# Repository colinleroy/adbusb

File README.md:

#  ADB to USB converter for Apple keyboards

Allow one ADB keyboard to be used on one ADB computer (old Macintosh and Apple IIgs) and one USB computer at the same time by switching between them.

## What works

- adb passthrough between a macintosh and keyboard/mouse + softpower
- adb keyboard to usb-hid conversion:
  - iso and ansi layouts
  - locking caps lock
  - power key in usb (translated as 0x66 "keyboard power")
- tested on multiple keyboards: aek ii, m0116/m0118, appledesign...
- tested on macintosh se
  
## What don't work yet

- keyboard leds on usb: the *keyboard* library doesn't handle hid output reports
- hotplugging adb: works randomly, the microcontroller don't seems to like that
- mouse passthrough in usb-hid mode
- correct keyboard detection by the macintosh when the board is in usb mode: not a problem in practice
- collision detection handling: the program calls the keyboard at address 2

## Hardware needed

- arduino pro micro because it works on 5V and is hid capable
- a resistor (1K - 10K ohm) for the pull up
- 2 mini-din 4 pin connectors
- 2-pin switch

## How to build it

- connect the switch between A3 (PF4) and GND
- connect GND on the two mini-din pins 4
- connect 9 (PB5) to the mini-din A pin 1 (computer adb line)
- connect 8 (PB4) to the mini-din A pin 2 (computer softpower line)
- connect VCC to the mini-din B pin 3 (keyboard power)
- connect 10 (PB6) to VCC through the resistor
- connect 10 (PB6) to the mini-din B pin 1 (keyboard adb line)
- connect 16 (PB2) to the mini-din B pin 2 (keyboard softpower line)
- mark the mini-din B as the keyboard connector

> [!CAUTION]
> i don't know what happens if you invert the connectors and inject external 5V into the macintosh adb

Mini-DIN female connector front view :
```
/------\
| 4  3 |
| 2  1 |
\__==__/
```

Arduino Pro Micro pinout :
```
                                ___________
                     PD3  TXD  |    USB    |  RAW
                     PD2   20  |           |  GND        --- keyboard pin 4
                          GND  |           |  RST
computer pin 4 ---        GND  |           |  VCC        --- keyboard pin 3 ---
                     PD1    2  |           |  A3   PF4                         |
                     PD0    3  |           |  A2   PF5                         _
                     PD4    4  |           |  A1   PF6                        | |
                     PC6    5  |           |  A0   PF7               resistor | |
                     PD7    6  |           |  15   PB1                        |_|
                     PE6    7  |           |  14   PB3                         |
computer pin 2 ---   PB4    8  |           |  16   PB2   --- keyboard pin 2    |
computer pin 1 ---   PB5    9  |___________|  10   PB6   --- keyboard pin 1 ---

```

## How to compile and upload it

1. install `arduino-cli`
2. `arduino-cli core install arduino:avr`
3. `arduino-cli lib install Keyboard`
4. compile this project by `cd` in then `arduino-cli compile --fqbn arduino:avr:micro`
5. connect the board to the computer
6. get board port with `arduino-cli board list`
7. upload it `arduino-cli upload -p /dev/.......`

## References

- [Guide to the Macintosh family hardware, Chapter 8 : Apple Desktop Bus, Apple, 1990](https://archive.org/details/apple-guide-macintosh-family-hardware/page/n325/mode/2up)
- [Apple Desktop Bus Protocol, lopaciuk.eu, 2021](https://www.lopaciuk.eu/2021/03/26/apple-adb-protocol.html)
- [Understanding the ADB Service Request Signal, bigmessowires, 2016](https://www.bigmessowires.com/2016/03/30/understanding-the-adb-service-request-signal/)
- [Apple Desktop Bus (ADB), wiki.preterhuman.net](https://wiki.preterhuman.net/Apple_Desktop_Bus_(ADB))

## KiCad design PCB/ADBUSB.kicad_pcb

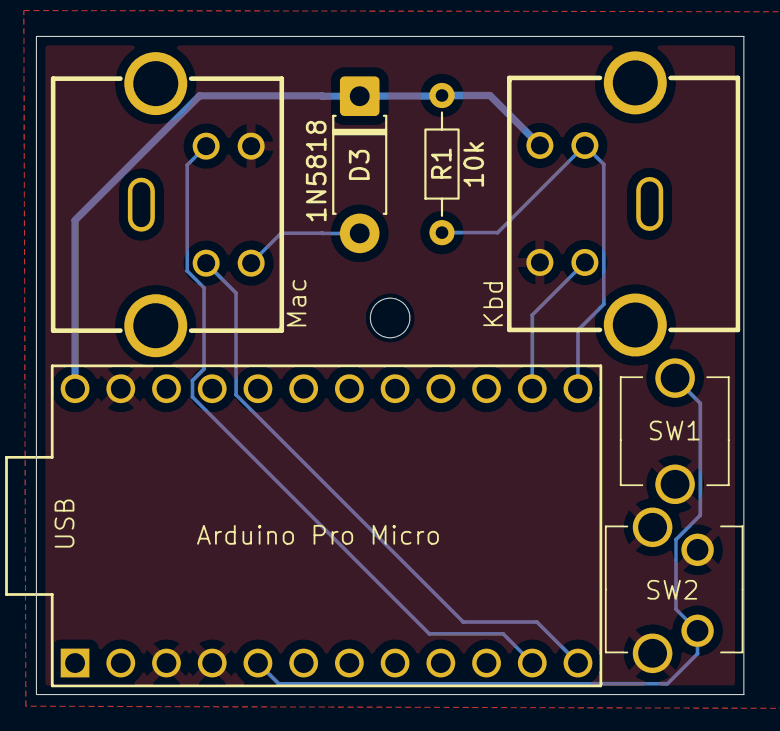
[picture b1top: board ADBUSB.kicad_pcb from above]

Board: 2 copper layers, 39.3 x 36.6 mm, 7 parts (0 on the bottom side), 8 nets.

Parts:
D3: 1N5818; D_DO-41_SOD81_P7.62mm_Horizontal
J1, J2: MLD-MDC-4-02
R1: 10k; R_Axial_DIN0204_L3.6mm_D1.6mm_P7.62mm_Horizontal
SW1: SW_SPST; SPST_power_switch_horizontal
SW2: SW_SPST; SPST_power_switch
U1: ProMicro

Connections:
GND: J1.4, J2.4, SW1.2, SW2.2, SW2.3, SW2.4 (3), U1.3 (GND), U1.4 (GND), U1.23 (GND)
unnamed: D3.2 (A), J1.3
unnamed: J2.2, U1.14 (B2)
unnamed: J1.2, U1.11 (B4)
unnamed: J1.1, U1.12 (B5)
unnamed: J2.1, R1.1, U1.13 (B6)
unnamed: SW1.1, SW2.1, U1.5 (SDA)
RAW_5V: D3.1 (K), J2.3, R1.2, U1.24 (RAW)

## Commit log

2026-06-21 initial files
2026-06-21 initial reset for M0116
2026-06-22 schematic
2026-06-24 Add PCB
2026-06-25 Add a second button footprint
    So one can either use an horizontal or vertical one
